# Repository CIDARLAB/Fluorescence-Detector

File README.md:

Fluorescence Detector

# Contents

1. Lockin-Amplifier - Full implementation of the Fluorescence Detector System
2. ADC Test Board - Test Board and default in sister board for ADC for V1 of the Lockin-Amplifier
3. Mod-Demod Test Board - Test board for the demodulator testing
4. Light Source Modulator Board - Board for Modulating the Light Source (LED/Laser)

# Locking Amplifier Specs

| Parameter                 	| Value              	|
|---------------------------	|--------------------	|
| #Channels                 	| 1                  	|
| Max Sampling Rate         	| 2.5 kHz            	|
| Amplification             	| x10^8 (140 dB)     	|
| SNR                       	| TBA                	|
| Input Voltage Noise       	| TBA                	|
| Input Impedance           	| TBA                	|
| Voltage Sensitivity Range 	| TBA to TBA         	|
| Minimum Step Size         	| TBA                	|
| ADC Resolution            	| 16 bit             	|
| ADC Interface             	| SPI (2 wire)       	|
| Supply Voltage            	| 24 V               	|
| Supply Current            	| 300 mA             	|
| Supply Pin                	| 2.5 mm Barrel Jack 	|

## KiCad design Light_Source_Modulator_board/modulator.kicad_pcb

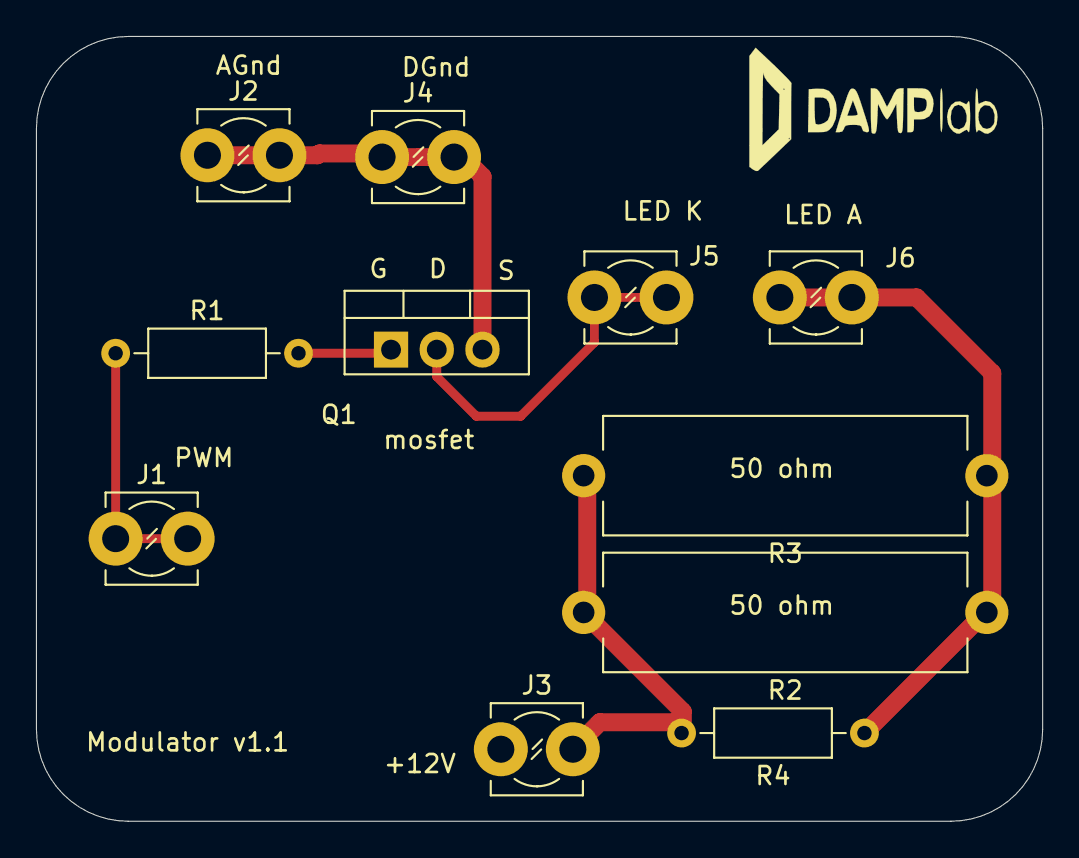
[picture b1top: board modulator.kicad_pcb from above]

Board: 2 copper layers, 55.9 x 43.6 mm, 12 parts (0 on the bottom side), 6 nets.

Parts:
G1: LOGO; damp_logo
J1, J2, J3, J4, J5, J6: Screw_Terminal_01x01; TerminalBlock_MetzConnect_360381_1x01_Horizontal_ScrewM3.0
Q1: FQP30N06L; TO-220-3_Vertical
R1: 1k; R_Axial_DIN0207_L6.3mm_D2.5mm_P10.16mm_Horizontal
R2, R3: 50; R_Axial_Power_L20.0mm_W6.4mm_P22.40mm
R4: 100; R_Axial_DIN0207_L6.3mm_D2.5mm_P10.16mm_Horizontal

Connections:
+12V: J3.1, R2.2, R3.2, R4.2
/pwm: J1.1, R1.1
GNDA: J2.1, J4.1, Q1.3
unnamed: J5.1, Q1.2
unnamed: J6.1, R2.1, R3.1, R4.1
unnamed: Q1.1, R1.2

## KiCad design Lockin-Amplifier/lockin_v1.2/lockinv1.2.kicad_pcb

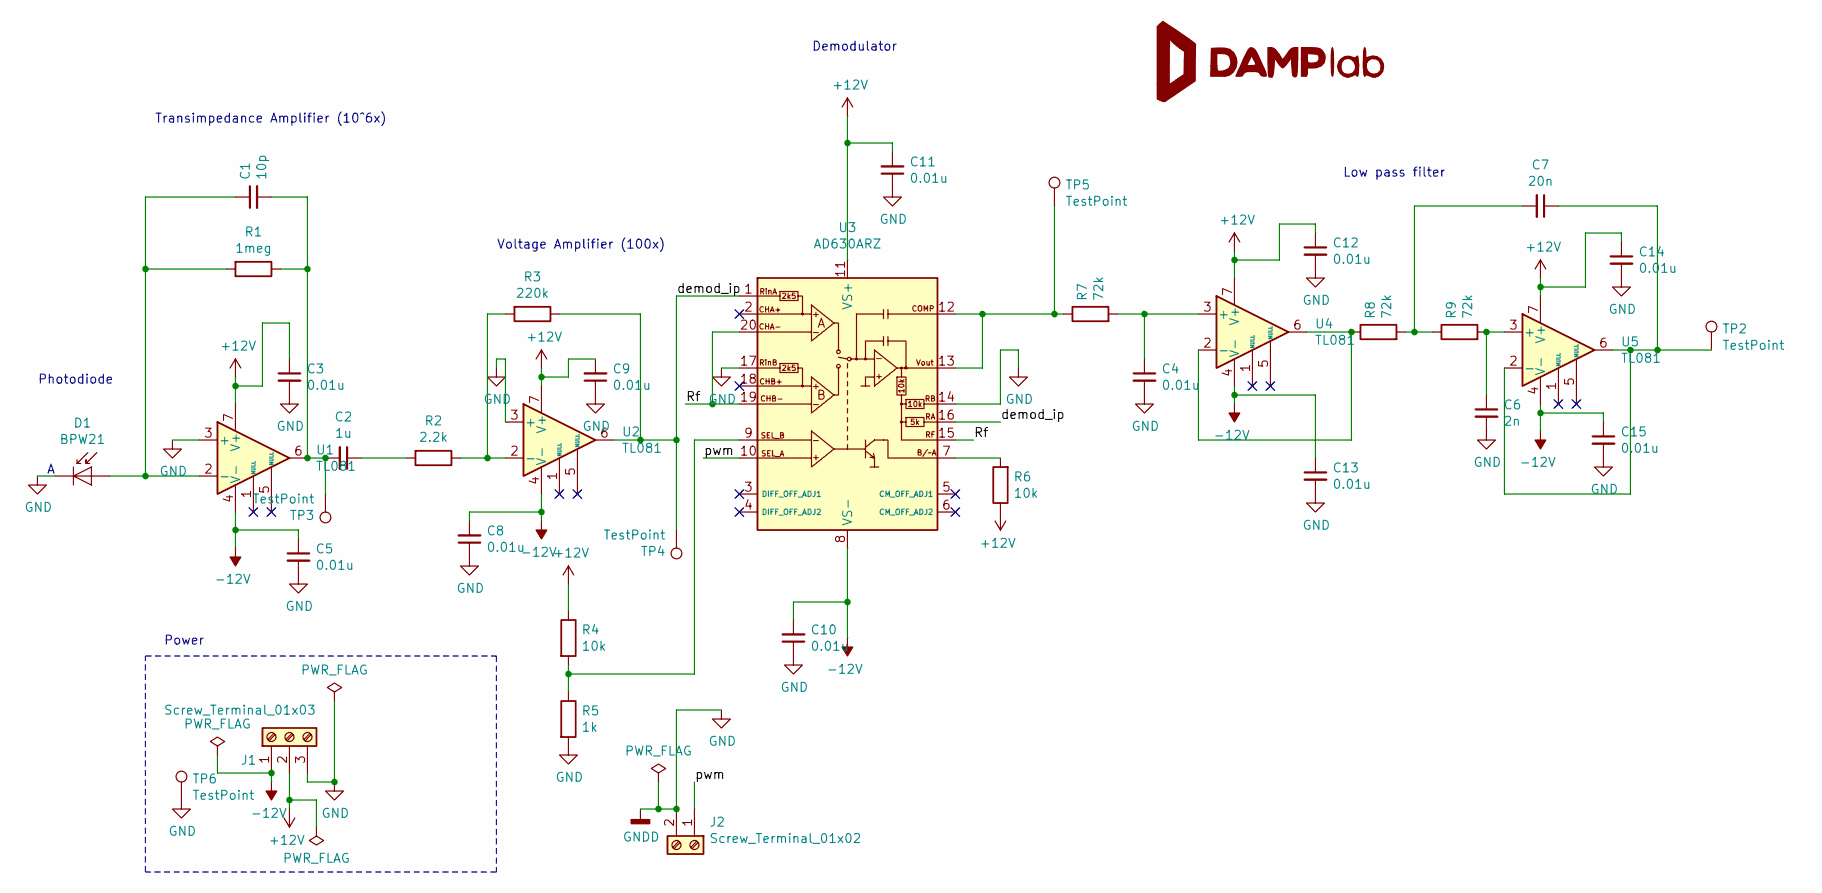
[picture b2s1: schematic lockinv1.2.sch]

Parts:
C1: 10p; C_Disc_D9.0mm_W2.5mm_P5.00mm
C2: 1u; C_Disc_D9.0mm_W2.5mm_P5.00mm
C3, C4, C5, C8, C9, C10, C11, C12, C13, C14, C15: 0.01u; C_Disc_D9.0mm_W2.5mm_P5.00mm
C6: 2n; C_Disc_D9.0mm_W2.5mm_P5.00mm
C7: 20n; C_Disc_D9.0mm_W2.5mm_P5.00mm
D1: BPW21; TO-5-2_Window
G1: LOGO; damp_logo
J1: Screw_Terminal_01x03; TerminalBlock_TE_282834-3_1x03_P2.54mm_Horizontal
J2: Screw_Terminal_01x02; TerminalBlock_TE_282834-2_1x02_P2.54mm_Horizontal
R1: 1meg; R_Axial_DIN0207_L6.3mm_D2.5mm_P10.16mm_Horizontal
R2: 2.2k; R_Axial_DIN0207_L6.3mm_D2.5mm_P10.16mm_Horizontal
R3: 220k; R_Axial_DIN0207_L6.3mm_D2.5mm_P10.16mm_Horizontal
R4, R6: 10k; R_Axial_DIN0207_L6.3mm_D2.5mm_P10.16mm_Horizontal
R5: 1k; R_Axial_DIN0207_L6.3mm_D2.5mm_P10.16mm_Horizontal
R7, R8, R9: 72k; R_Axial_DIN0207_L6.3mm_D2.5mm_P10.16mm_Horizontal
TP2, TP3, TP4, TP5, TP6: TestPoint; TestPoint_Loop_D2.50mm_Drill1.85mm
U1, U2, U4, U5: TL081; DIP-8_W7.62mm
U3: AD630ARZ; DIP-20_W7.62mm

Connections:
+12V: C3.1, C9.2, C11.2, C12.1, C14.1, J1.2, R4.1, R6.1, U1.7 (V+), U2.7 (V+), U3.11 (VS+), U4.7 (V+), U5.7 (V+)
-12V: C5.1, C8.2, C10.2, C13.1, C15.1, J1.1, U1.4 (V-), U2.4 (V-), U3.8 (VS-), U4.4 (V-), U5.4 (V-)
/Rf: U3.15 (RF), U3.19 (CHB-), U3.20 (CHA-)
/demod_ip: R3.1, TP4.1, U2.6, U3.1 (RinA), U3.16 (RA)
/pwm: J2.1, U3.10 (SEL_A)
GND: C3.2, C4.2, C5.2, C6.2, C8.1, C9.1, C10.1, C11.1, C12.2, C13.2, C14.2, C15.2, D1.1 (K), J1.3, J2.2, R5.2, TP6.1, U1.3 (+), U2.3 (+), U3.14 (RB), U3.17 (RinB)
unnamed: C1.1, D1.2 (A), R1.2, U1.2 (-)
unnamed: C1.2, C2.2, R1.1, TP3.1, U1.6
unnamed: C2.1, R2.2
unnamed: C4.1, R7.2, U4.3 (+)
unnamed: C6.1, R9.2, U5.3 (+)
unnamed: C7.1, TP2.1, U5.2 (-), U5.6
unnamed: C7.2, R8.2, R9.1
unnamed: R2.1, R3.2, U2.2 (-)
unnamed: R4.2, R5.1, U3.9 (SEL_B)
unnamed: R6.2, U3.7 (B/~A)
unnamed: R7.1, TP5.1, U3.12 (COMP), U3.13 (Vout)
unnamed: R8.1, U4.2 (-), U4.6

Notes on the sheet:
Demodulator
Low pass filter
Photodiode
Power
Voltage Amplifier (100x)
Transimpedance Amplifier (10^6x)

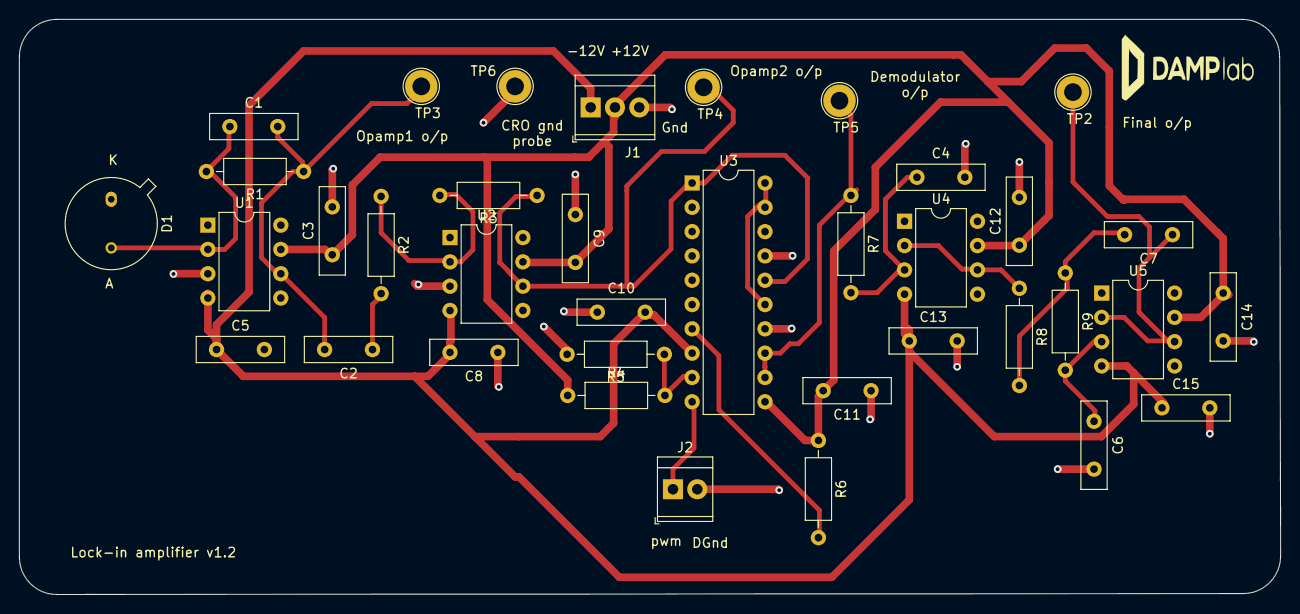
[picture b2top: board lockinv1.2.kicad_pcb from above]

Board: 2 copper layers, 131.8 x 60.1 mm, 38 parts (0 on the bottom side), 18 nets.

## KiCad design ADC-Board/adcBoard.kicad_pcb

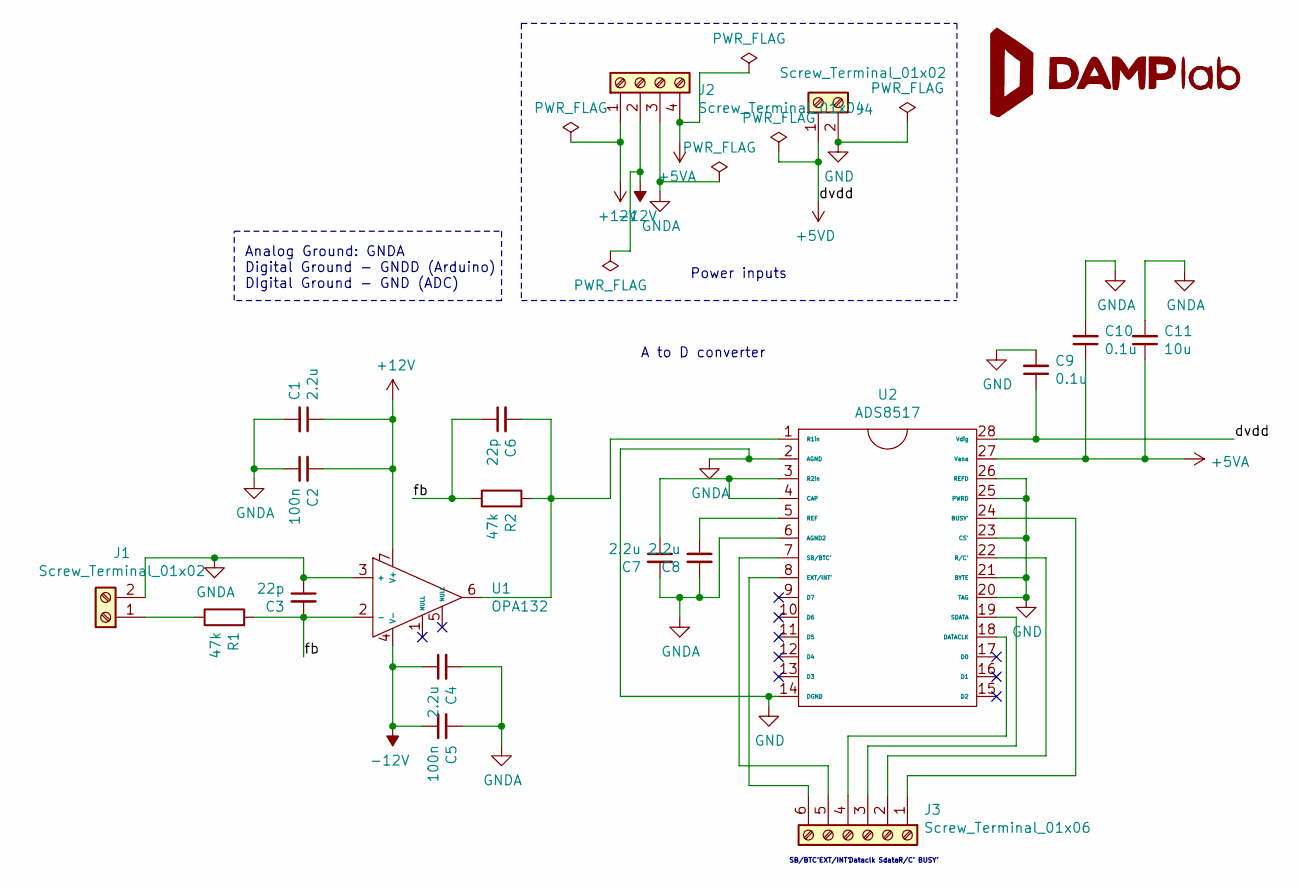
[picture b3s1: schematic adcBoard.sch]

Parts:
C1, C4, C7, C8: 2.2u; CP_Radial_Tantal_D5.5mm_P2.50mm
C2, C5: 100n; C_Disc_D9.0mm_W2.5mm_P5.00mm
C3, C6: 22p; C_Disc_D9.0mm_W2.5mm_P5.00mm
C9, C10: 0.1u; C_Disc_D9.0mm_W2.5mm_P5.00mm
C11: 10u; CP_Radial_Tantal_D5.5mm_P2.50mm
G1: LOGO; damp_logo
J1, J4: Screw_Terminal_01x02; TerminalBlock_TE_282834-2_1x02_P2.54mm_Horizontal
J2: Screw_Terminal_01x04; TerminalBlock_TE_282834-4_1x04_P2.54mm_Horizontal
J3: Screw_Terminal_01x06; TerminalBlock_TE_282834-6_1x06_P2.54mm_Horizontal
R1, R2: 47k; R_Axial_DIN0207_L6.3mm_D2.5mm_P10.16mm_Horizontal
U1: OPA132; SOIC-8_3.9x4.9mm_P1.27mm
U2: ADS8517; TSSOP-28_4.4x9.7mm_P0.65mm

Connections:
+5VA: C10.1, C11.1, J2.4, U2.27 (Vana)
+5VD: C9.1, J4.1, U2.28 (Vdig)
+12V: C1.1, C2.2, J2.1, U1.7 (V+)
-12V: C4.1, C5.1, J2.2, U1.4 (V-)
/fb: C3.2, C6.1, R1.2, R2.1, U1.2 (-)
GND: C1.2, C2.1, C3.1, C4.2, C5.2, C7.2, C8.2, C9.2, C10.2, C11.2, J1.2, J2.3, J4.2, U1.3 (+), U2.2 (AGND), U2.6 (AGND2), U2.14 (DGND), U2.20 (TAG), U2.21 (BYTE), U2.23 (CS'), U2.25 (PWRD), U2.26 (REFD)
unnamed: C6.2, R2.2, U1.6, U2.1 (R1in)
unnamed: C7.1, U2.3 (R2in), U2.4 (CAP)
unnamed: C8.1, U2.5 (REF)
unnamed: J1.1, R1.1
unnamed: J3.1, U2.24 (BUSY')
unnamed: J3.2, U2.22 (R/C')
unnamed: J3.3, U2.19 (SDATA)
unnamed: J3.4, U2.18 (DATACLK)
unnamed: J3.5, U2.7 (SB/BTC')
unnamed: J3.6, U2.8 (EXT/INT')

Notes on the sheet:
Analog Ground: GNDA Digital Ground - GNDD (Arduino) DIgital Ground - GND (ADC)
Power inputs
SB/BTC'
EXT/INT'
Dataclk
Sdata
R/C'
BUSY'
A to D converter

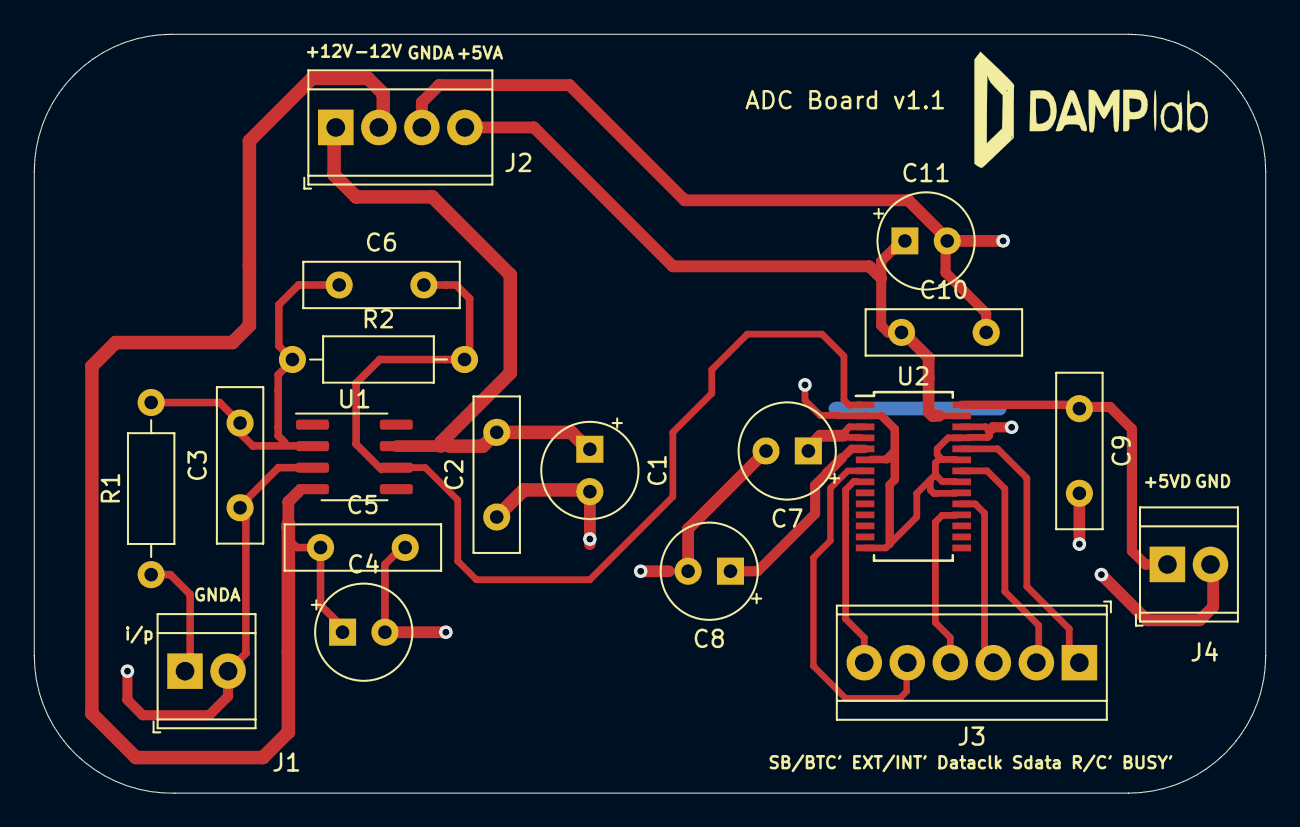
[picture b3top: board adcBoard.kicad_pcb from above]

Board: 2 copper layers, 72.7 x 44.8 mm, 20 parts (0 on the bottom side), 16 nets.

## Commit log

2019-10-28 Lock in PCB v1.1
2019-11-25 .gitignore is now working
2019-11-25 Rename folder
2019-12-10 Renamed the folder to Lockin Amplifier
2019-12-10 Added Readme and Lisence
2019-12-23 Adding ADC board v1.1
2019-12-23 Reverting to 5639559f49259e50b6b5cf6be8fd6d8661ee3bd0
2019-12-23 ADC Kicad files
2019-12-29 Rearranging lockin amp folder
2019-12-29 Lock-in PCB v1.2
2020-01-01 Modulator Kicad files and gerbers
2020-01-01 Papers
2020-01-01 Datasheets
2020-01-01 Renamed modulator
2020-01-01 List of Materials
2020-01-01 Handoff Notes
